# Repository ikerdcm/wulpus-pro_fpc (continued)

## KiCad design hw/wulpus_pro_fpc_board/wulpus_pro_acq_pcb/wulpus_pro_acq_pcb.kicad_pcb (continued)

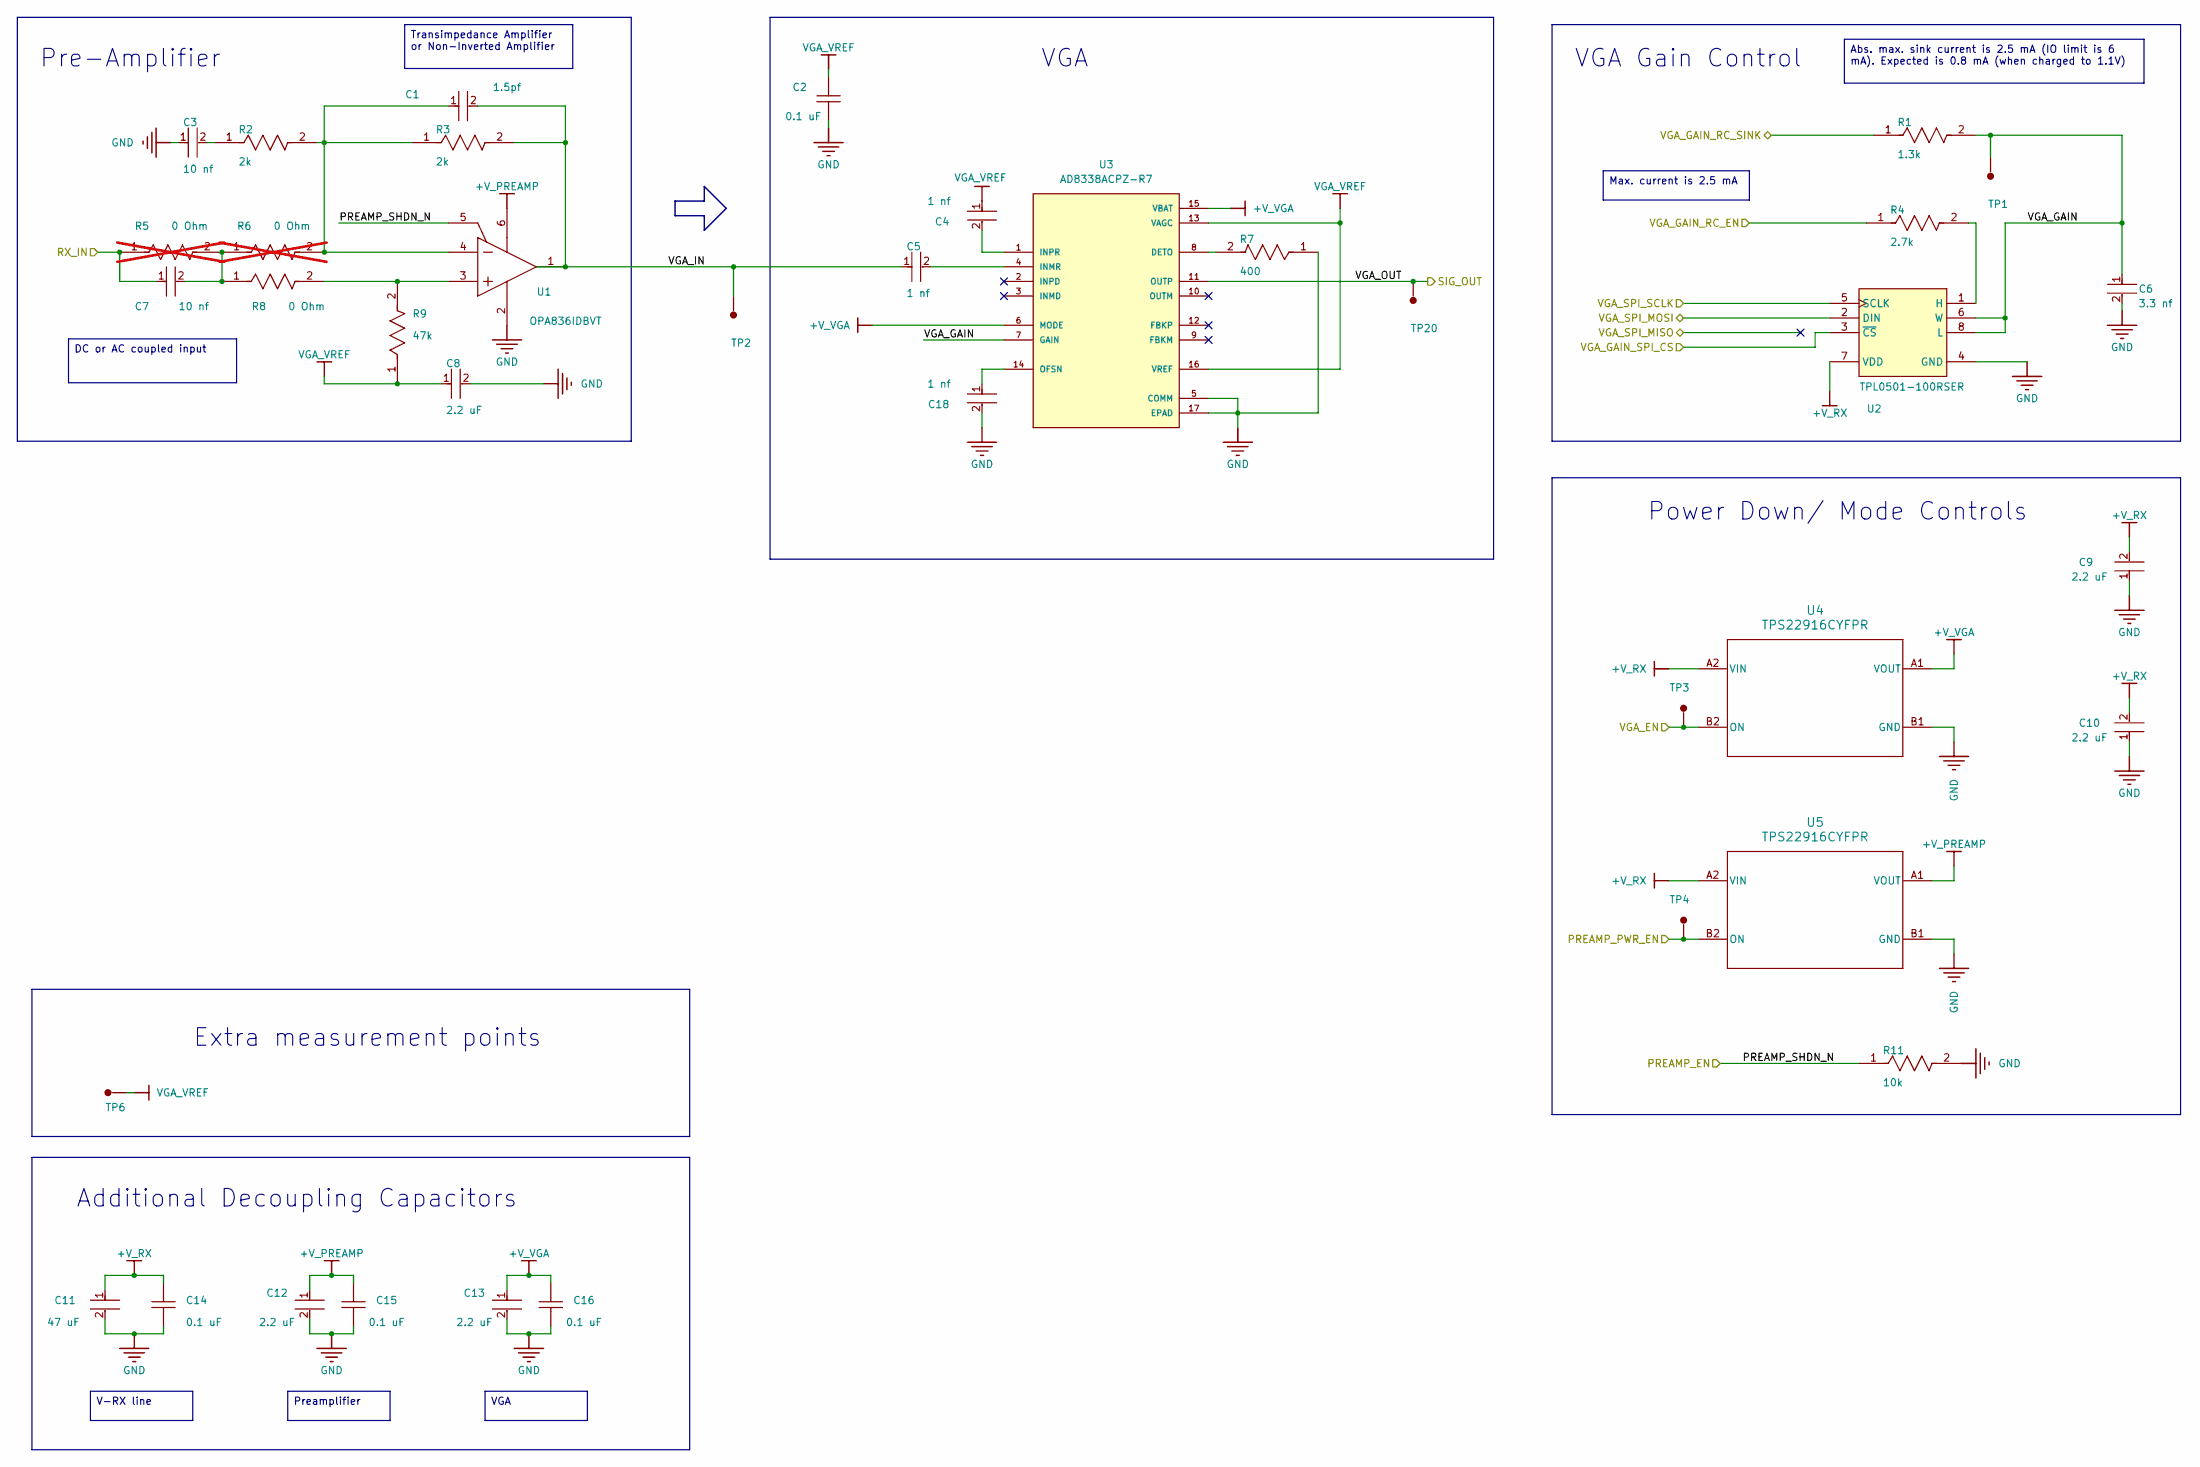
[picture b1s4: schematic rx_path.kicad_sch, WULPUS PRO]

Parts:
C1: 1.5pf; C_0402_1005Metric; VOLTAGE RATING 50V; VOLTAGE RATING (DC) 50V; PART NUMBER GJM1555C1H1R5BB01D
C2, C14, C15, C16: 0.1 uF; C_0402_1005Metric; PART NUMBER C0402C104K4RACTU
C3, C7: 10 nf; C_0402_1005Metric; VOLTAGE 10V; VOLTAGE RATING (DC) 10V; PART NUMBER GRM033R71A103KA01D
C4, C5, C18: 1 nf; C_0402_1005Metric; TOLERANCE 5%; VOLTAGE RATING 50V; PART NUMBER GRM1555C1H102JA01D
C6: 3.3 nf; C_0402_1005Metric; VOLTAGE RATING 50V; TOLERANCE 5%; PART NUMBER 04025C332JAT2A
C8, C9, C10, C12, C13: 2.2 uF; C_0402_1005Metric; VOLTAGE RATING 10V; VOLTAGE RATING (DC) 10V; PART NUMBER C1005X7S1A225K050BC
C11: 47 uF; C_0603_1608Metric; TOLERANCE 20%; VOLTAGE RATING (DC) 6.3V; PART NUMBER GRM188R60J476ME01D
R1: 1.3k; R_0402_1005Metric; TOLERANCE 5%; VOLTAGE RATING (DC) 50V; MPN CRCW04021K30JNED
R2, R3: 2k; R_0402_1005Metric; WORKING VOLTAGE 50V; POWER RATING 100mW; MPN ERJ-2RKF2001X
R4: 2.7k; R_0402_1005Metric; TOLERANCE 1%; MPN MCS04020C2701FE000
R5, R6: 0 Ohm; R_0402_1005Metric; TOLERANCE 5%; VOLTAGE RATING 50V; MPN CRCW04020000Z0ED; not fitted
R7: 400; R_0402_1005Metric; TOLERANCE 1%; VOLTAGE RATING 50V; MPN CRCW04021R00FKEDC
R8: 0 Ohm; R_0402_1005Metric; TOLERANCE 5%; VOLTAGE RATING 50V; MPN CRCW04020000Z0ED
R9: 47k; R_0402_1005Metric; POWER RATING 50mW; TOLERANCE 5%; MPN CRCW040247K0JNEE
R11: 10k; R_0402_1005Metric; VOLTAGE RATING 50V; POWER RATING 63mW; MPN CRCW040210K0JNED
TP1, TP2, TP3, TP4, TP6, TP20: TP-SM-C-100; TestPoint_Pad_D1.0mm
U1: OPA836IDBVT; SOT-23-6_Handsoldering; PARTNUMBER OPA836IDBVT
U2: TPL0501-100RSER; Texas_UQFN-8_1.5x1.5mm_P0.5mm; PARTNUMBER TPL0501-100RSER
U3: AD8338ACPZ-R7; QFN50P300X300X80-17N; PARTREV B; DigiKey_Part_Number 505-AD8338ACPZ-R7CT-ND
U4, U5: TPS22916CYFPR; YFP0004ABAB; MPN TPS22916CYFPR; LCSC C2680319

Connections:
+V_PREAMP: C12.1, C15.2, U1.6 (VS+), U5.A1 (VOUT)
+V_RX: C9.2, C10.2, C11.1, C14.2, U2.7 (VDD), U4.A2 (VIN), U5.A2 (VIN); also elsewhere on the board
+V_VGA: C13.1, C16.2, U3.6 (MODE), U3.15 (VBAT), U4.A1 (VOUT)
/U_hv_mux_tr_sw/HV_MUX_SPI_MISO: U2.2 (DIN); also elsewhere on the board
/U_hv_mux_tr_sw/HV_MUX_SPI_SCLK: U2.5 (SCLK); also elsewhere on the board
/U_hv_mux_tr_sw/RX_OUT: C7.1, R5.1; also elsewhere on the board
/U_msp430/PREAMP_PWR_EN: TP4.1 (1_1), U5.B2 (ON); also elsewhere on the board
/U_msp430/VGA_GAIN_RC_EN: R4.1; also elsewhere on the board
/U_msp430/VGA_GAIN_RC_SINK: R1.1; also elsewhere on the board
/U_msp430/VGA_GAIN_SPI_CS: U2.3 (~CS); also elsewhere on the board
/U_msp430/VGA_PWR_EN: TP3.1, U4.B2 (ON); also elsewhere on the board
/U_rx_path/PREAMP_SHDN_N: R11.1, U1.5 (~PD); also elsewhere on the board
/U_rx_path/VGA_GAIN: C6.1, R1.2, TP1.1, U2.6 (W), U2.8 (L), U3.7 (GAIN)
/U_rx_path/VGA_IN: C1.2, C5.1, R3.2, TP2.1 (1_1), U1.1 (VOUT)
/U_rx_path/VGA_OUT: TP20.1 (1_1), U3.11 (OUTP); also elsewhere on the board
GND: C2.1, C3.1, C6.2, C8.2, C9.1, C10.1, C11.2, C12.2, C13.2, C14.1, C15.1, C16.1, C18.2, R7.1, R11.2, U1.2 (VS-), U2.4 (GND), U3.5 (COMM), U3.17 (EPAD), U4.B1 (GND), U5.B1 (GND); also elsewhere on the board
unnamed: C3.2, R2.1
unnamed: C7.2, R5.2, R6.1, R8.1
unnamed: R8.2, R9.2, U1.3 (VIN+)
unnamed: C1.1, R2.2, R3.1, R6.2, U1.4 (VIN-)
unnamed: R4.2, U2.1 (H)
unnamed: R7.2, U3.8 (DETO)
unnamed: C5.2, U3.4 (INMR)
unnamed: C4.2, U3.1 (INPR)
unnamed: C18.1, U3.14 (OFSN)
VGA_VREF: C2.2, C4.1, C8.1, R9.1, TP6.1 (1_1), U3.13 (VAGC), U3.16 (VREF)

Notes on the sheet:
VGA Gain Control
Power Down/ Mode Controls
Additional Decoupling Capacitors
Pre-Amplifier
Extra measurement points
VGA
Max. current is 2.5 mA
V-RX line
Abs. max. sink current is 2.5 mA (IO limit is 6 mA). Expected is 0.8 mA (when charged to 1.1V)
DC or AC coupled input
Preamplifier
Transimpedance Amplifier or Non-Inverted Amplifier

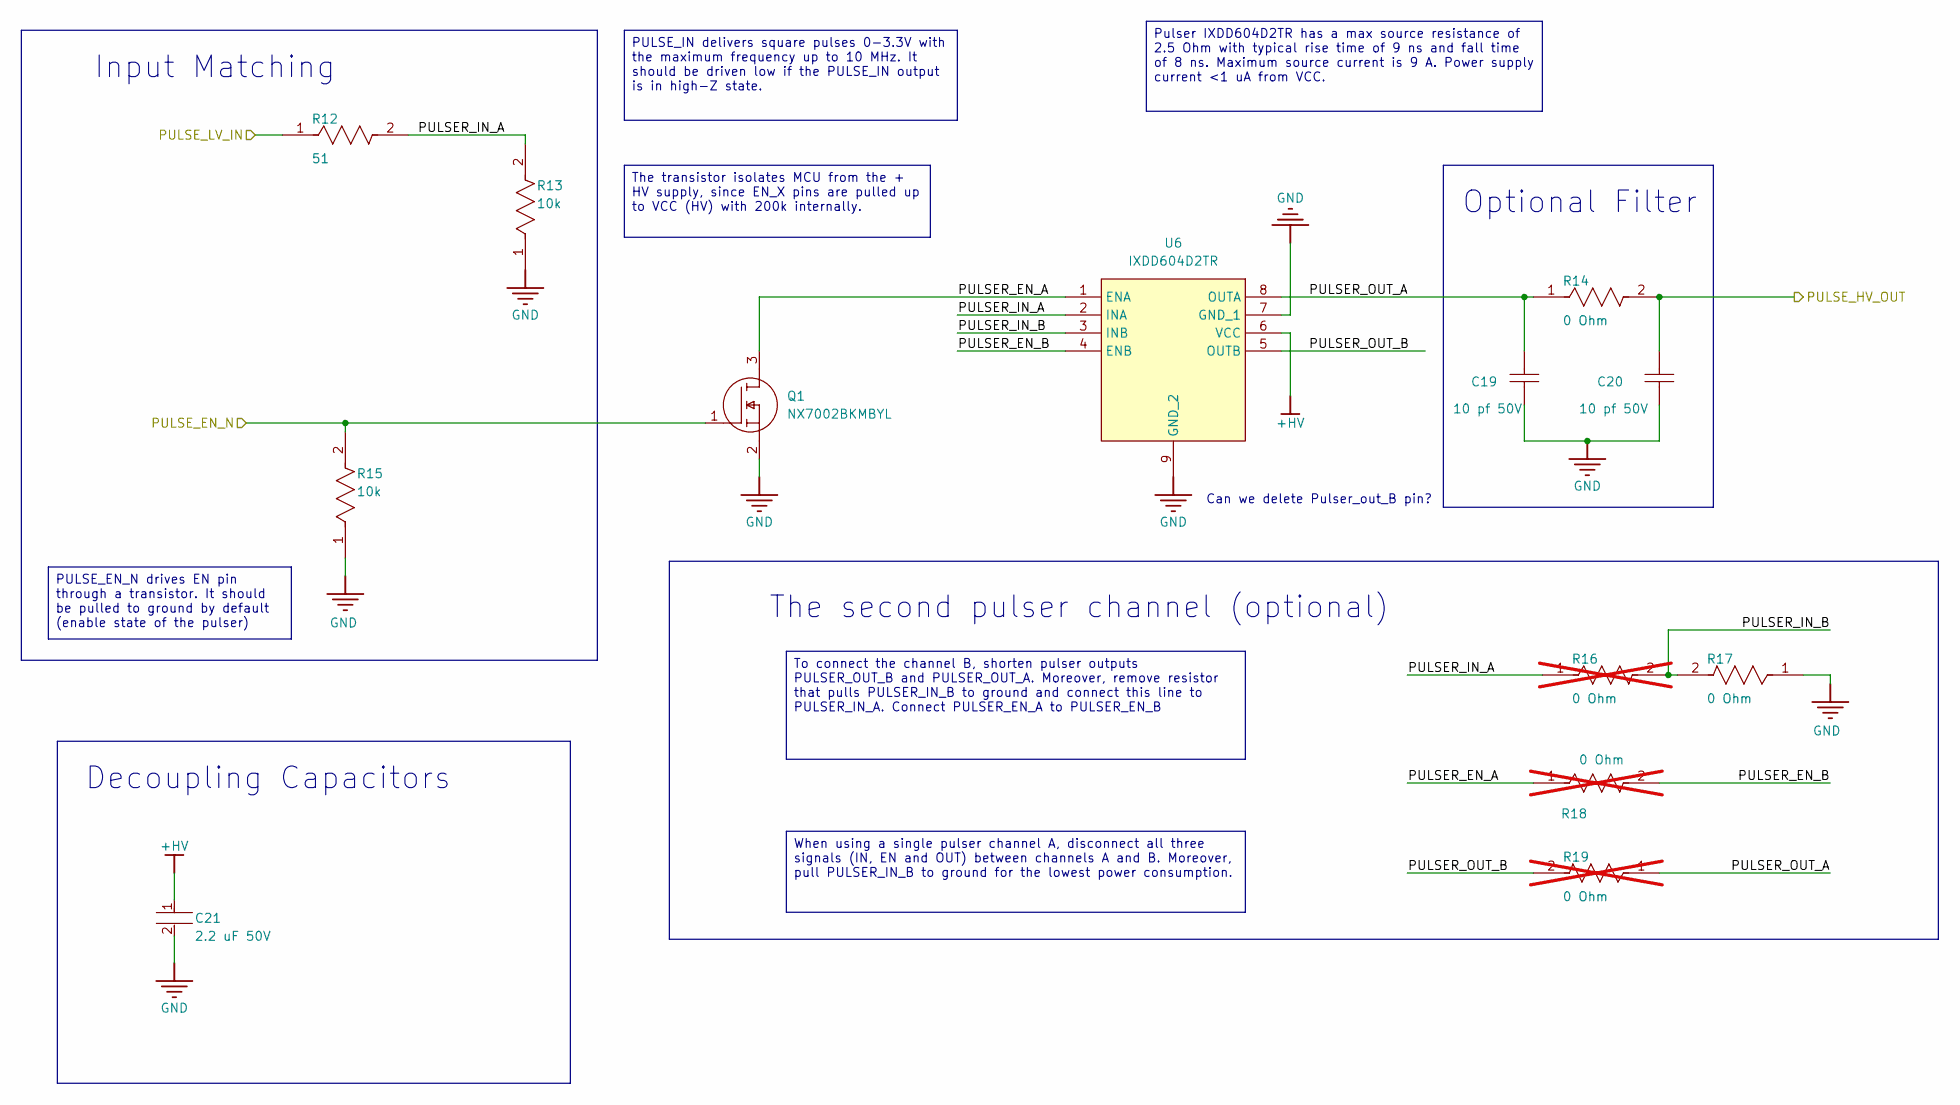
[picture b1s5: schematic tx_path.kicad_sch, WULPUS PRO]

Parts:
C19, C20: 10 pf 50V; C_0402_1005Metric; PART NUMBER GRM1555C1H100JA01D
C21: 2.2 uF 50V; C_0603_1608Metric; VOLTAGE RATING (DC) 50V; TOLERANCE 20%; PART NUMBER GRM188R61H225ME11D
Q1: NX7002BKMBYL; Diodes_DFN1006-3; MANUFACTURER_PART_NUMBER NX7002BKMBYL; MOUSER PART NUMBER 771-NX7002BKMBYL
R12: 51; R_0402_1005Metric; TOLERANCE 5%; POWER RATING 63mW; MPN CRCW040251R0JNED
R13, R15: 10k; R_0402_1005Metric; VOLTAGE RATING 50V; POWER RATING 63mW; MPN CRCW040210K0JNED
R14: 0 Ohm; R_0603_1608Metric; TOLERANCE 5%; VOLTAGE RATING 75V; MANUFACTURER PART NUMBER ERJ-3GEY0R00V; MOUSER DESCRIPTION Resistor, Chip Thick Film, 0 Ohm, 0.1w,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
R16, R18, R19: 0 Ohm; R_0402_1005Metric; TOLERANCE 5%; VOLTAGE RATING 50V; MPN CRCW04020000Z0ED; not fitted
R17: 0 Ohm; R_0402_1005Metric; TOLERANCE 5%; VOLTAGE RATING 50V; MPN CRCW04020000Z0ED
U6: IXDD604D2TR; IXYS_DFN-8_IXY; MANUFACTURER_PART_NUMBER IXDD604D2TR; MOUSER PART NUMBER 849-IXDD604D2TR

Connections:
+HV: C21.1, U6.6 (VCC); also elsewhere on the board
/U_hv_mux_tr_sw/TX_HV_PULSE_IN: C20.2, R14.2; also elsewhere on the board
/U_msp430/PULSER_HIZ_EN: Q1.1 (G), R15.2; also elsewhere on the board
/U_msp430/PULSER_OUT: R12.1; also elsewhere on the board
/U_tx_path/PULSER_EN_A: Q1.3 (D), R18.1, U6.1 (ENA)
/U_tx_path/PULSER_EN_B: R18.2, U6.4 (ENB)
/U_tx_path/PULSER_IN_A: R12.2, R13.2, R16.1, U6.2 (INA)
/U_tx_path/PULSER_IN_B: R16.2, R17.2, U6.3 (INB)
/U_tx_path/PULSER_OUT_A: C19.2, R14.1, R19.1, U6.8 (OUTA)
/U_tx_path/PULSER_OUT_B: R19.2, U6.5 (OUTB)
GND: C19.1, C20.1, C21.2, Q1.2 (S), R13.1, R15.1, R17.1, U6.7 (GND_1), U6.9 (GND_2); also elsewhere on the board

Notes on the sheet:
Can we delete Pulser_out_B pin?
The second pulser channel (optional)
Decoupling Capacitors
Input Matching
Optional Filter
PULSE_EN_N drives EN pin through a transistor. It should be pulled to ground by default (enable state of the pulser)
To connect the channel B, shorten pulser outputs PULSER_OUT_B and PULSER_OUT_A. Moreover, remove resistor that pulls PULSER_IN_B to ground and connect this line to PULSER_IN_A. Connect PULSER_EN_A to PULSER_EN_B
The transistor isolates MCU from the + HV supply, since EN_X pins are pulled up to VCC (HV) with 200k internally.
PULSE_IN delivers square pulses 0-3.3V with the maximum frequency up to 10 MHz. It should be driven low if the PULSE_IN output is in high-Z state.
Pulser IXDD604D2TR has a max source resistance of 2.5 Ohm with typical rise time of 9 ns and fall time of 8 ns. Maximum source current is 9 A. Power supply current <1 uA from VCC.
When using a single pulser channel A, disconnect all three signals (IN, EN and OUT) between channels A and B. Moreover, pull PULSER_IN_B to ground for the lowest power consumption.

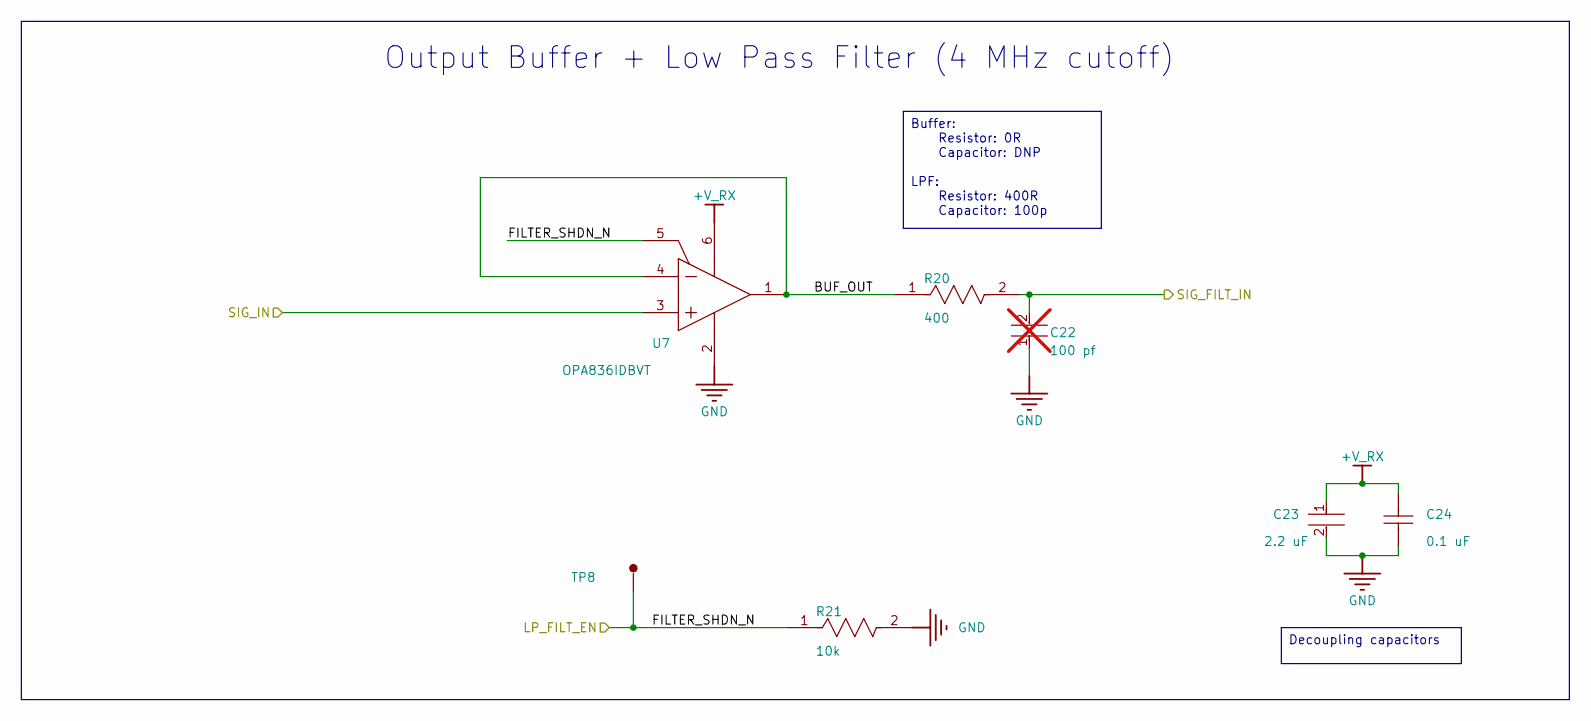
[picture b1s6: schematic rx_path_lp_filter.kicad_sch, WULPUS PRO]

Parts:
C22: 100 pf; C_0402_1005Metric; VOLTAGE 50V; TOLERANCE 1%; PART NUMBER 04025A101FAT2A; not fitted
C23: 2.2 uF; C_0402_1005Metric; VOLTAGE RATING 10V; VOLTAGE RATING (DC) 10V; PART NUMBER C1005X7S1A225K050BC
C24: 0.1 uF; C_0402_1005Metric; PART NUMBER C0402C104K4RACTU
R20: 400; R_0402_1005Metric; TOLERANCE 1%; VOLTAGE RATING 50V; MPN CRCW04021R00FKEDC
R21: 10k; R_0402_1005Metric; VOLTAGE RATING 50V; POWER RATING 63mW; MPN CRCW040210K0JNED
TP8: TP-SM-C-100; TestPoint_Pad_D1.0mm
U7: OPA836IDBVT; SOT-23-6_Handsoldering; PARTNUMBER OPA836IDBVT

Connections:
+V_RX: C23.1, C24.2, U7.6 (VS+); also elsewhere on the board
/U_msp430/ADC_IN: C22.2, R20.2; also elsewhere on the board
/U_rx_path/VGA_OUT: U7.3 (VIN+); also elsewhere on the board
/U_rx_path_lp_filter/BUF_OUT: R20.1, U7.1 (VOUT), U7.4 (VIN-)
/U_rx_path_lp_filter/FILTER_SHDN_N: R21.1, TP8.1, U7.5 (~PD); also elsewhere on the board
GND: C22.1, C23.2, C24.1, R21.2, U7.2 (VS-); also elsewhere on the board

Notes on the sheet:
Output Buffer + Low Pass Filter (4 MHz cutoff)
Decoupling capacitors
Buffer: Resistor: 0R Capacitor: DNP LPF: Resistor: 400R Capacitor: 100p

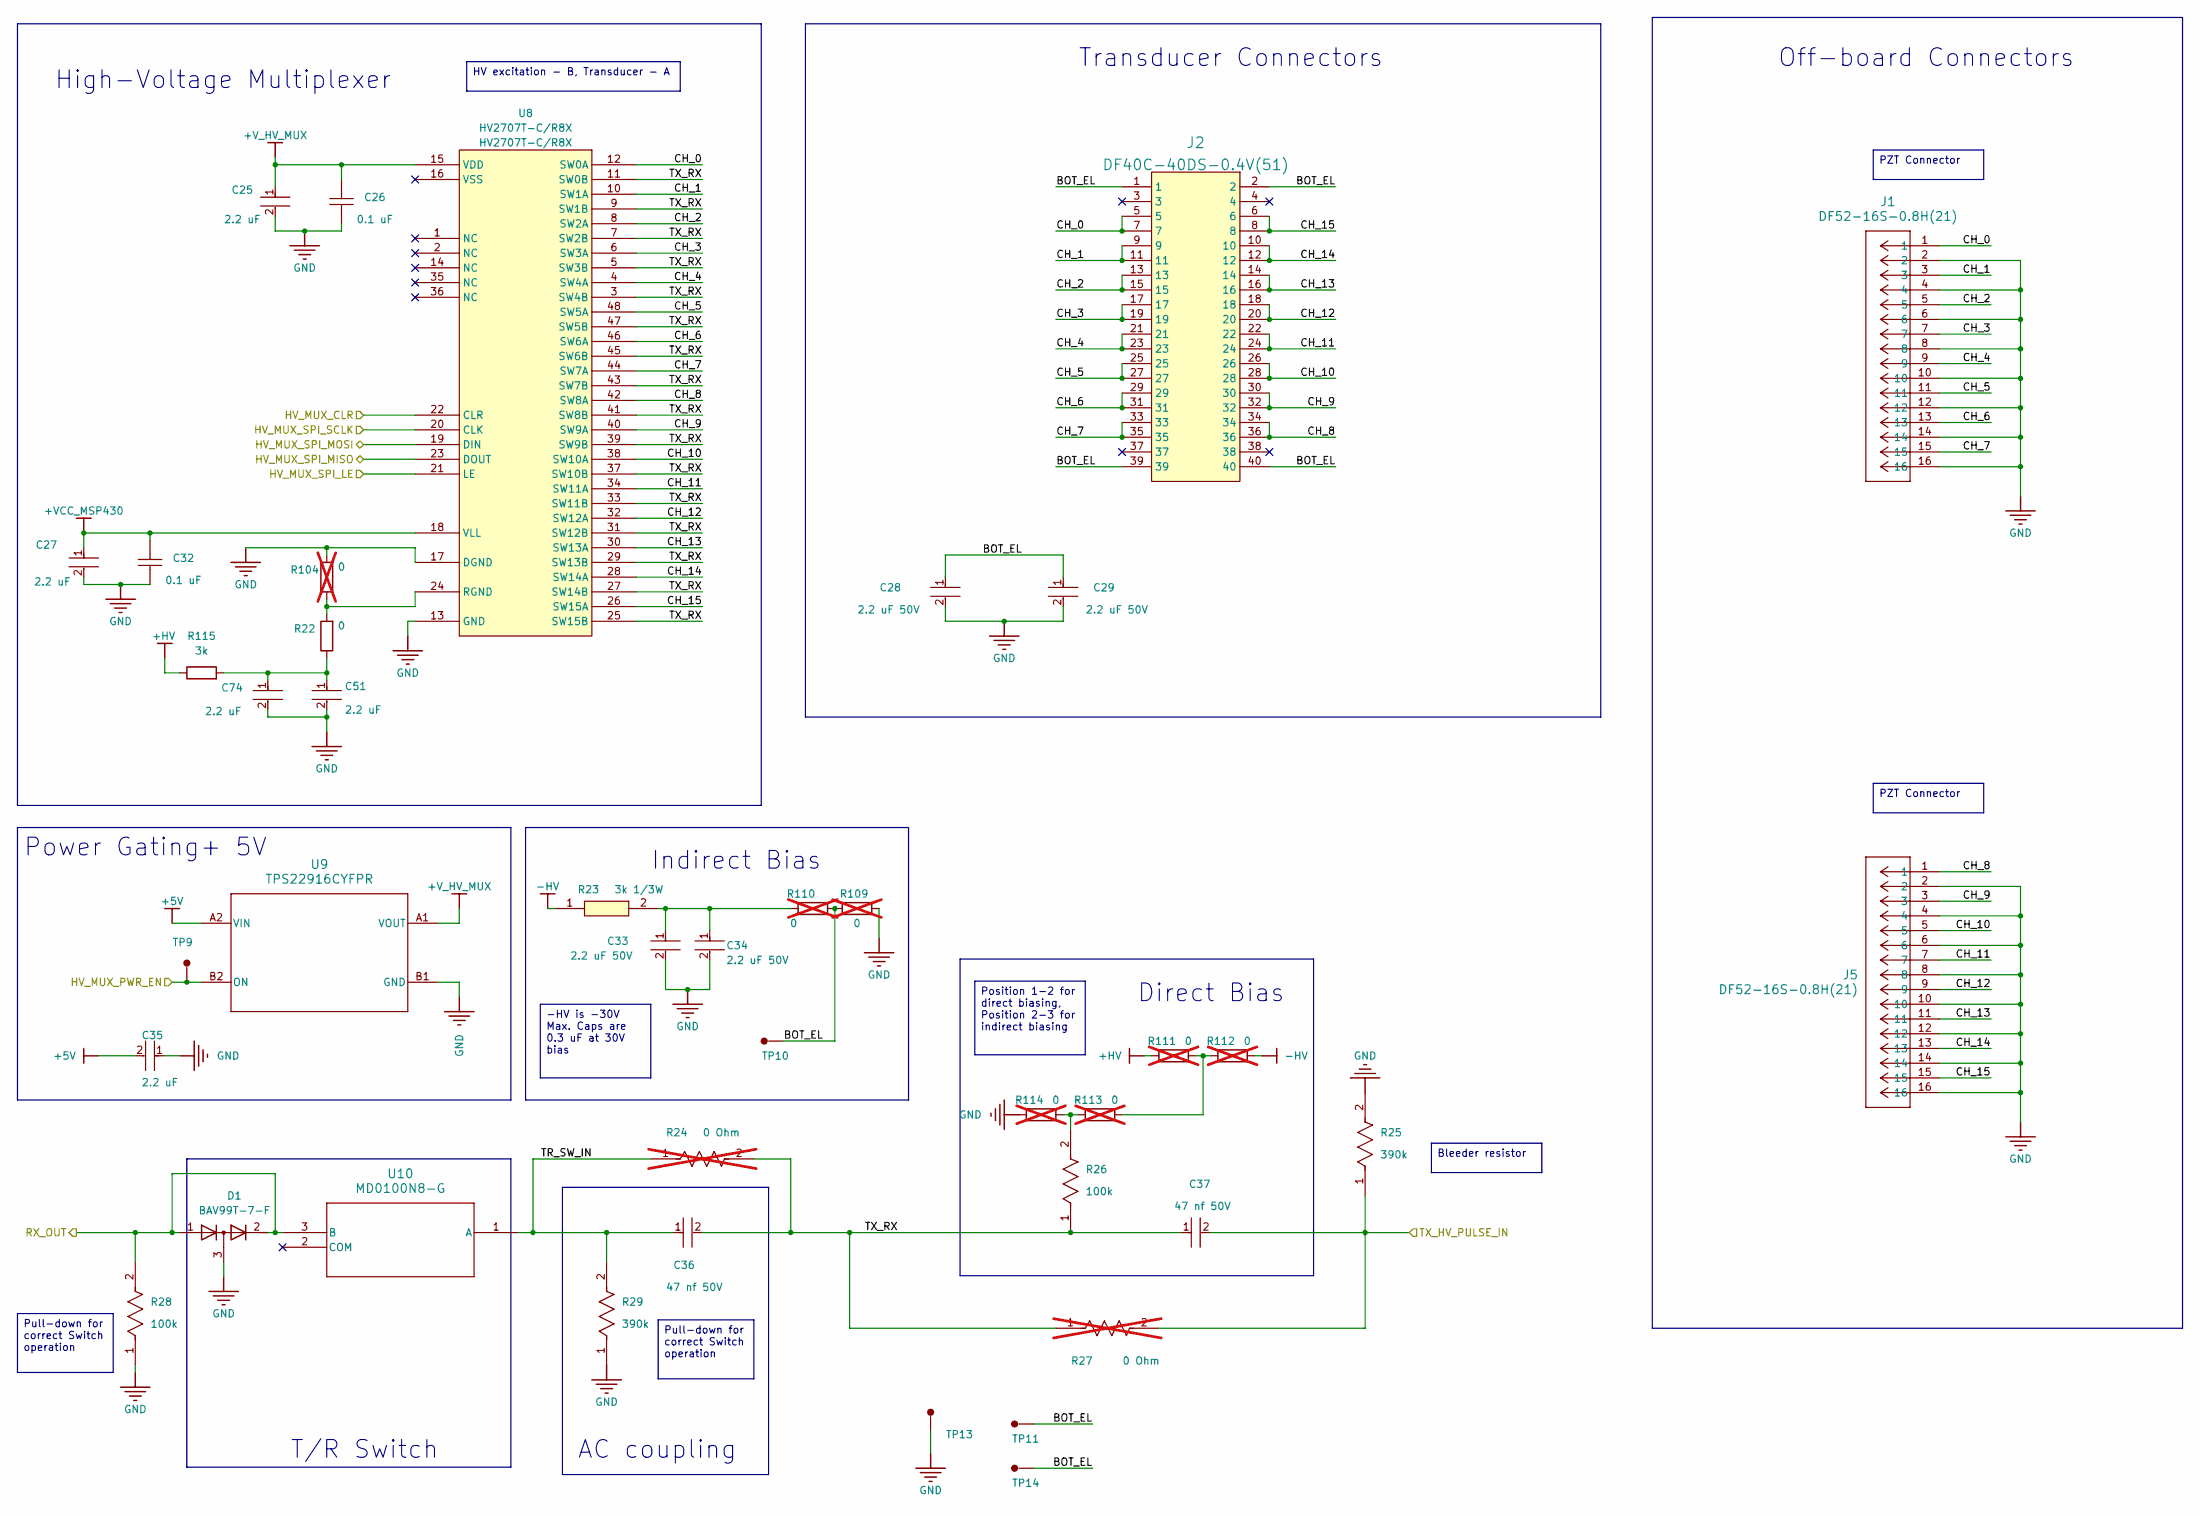
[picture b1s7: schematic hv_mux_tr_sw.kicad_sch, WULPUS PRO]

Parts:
C25, C27, C35, C51, C74: 2.2 uF; C_0402_1005Metric; VOLTAGE RATING 10V; VOLTAGE RATING (DC) 10V; PART NUMBER C1005X7S1A225K050BC
C26, C32: 0.1 uF; C_0402_1005Metric; PART NUMBER C0402C104K4RACTU
C28, C29, C33, C34: 2.2 uF 50V; C_0603_1608Metric; VOLTAGE RATING (DC) 50V; TOLERANCE 20%; PART NUMBER GRM188R61H225ME11
C36, C37: 47 nf 50V; C_0402_1005Metric; TOLERANCE 20%; VOLTAGE RATING (DC) 50V; PART NUMBER GRM155R71H473ME14D
D1: BAV99T-7-F; SOT-523; MPN BAV99T-7-F
J1, J5: DF52-16S-0.8H(21); CONN_DF52-16S-0.8H21_HIR; MPN DF52-16S-0.8H(21); LCSC C22281399
J2: DF40C-40DS-0.4V(51); Hirose_DF40C-40DS-0.4V_2x20_P0.4mm; MPN DF40C-40DS-0.4V(51)
R22: 0; R_0402_1005Metric; Tolerance 5%; MPN ERJ-2GE0R00X; LCSC C17168
R23: 3k 1/3W; R_0603_1608Metric; MANUFACTURER_PART_NUMBER ERJ-PA3J302V; MOUSER PART NUMBER 667-ERJ-PA3J302V
R24, R27: 0 Ohm; R_0402_1005Metric; TOLERANCE 5%; VOLTAGE RATING 50V; MPN CRCW04020000Z0ED; not fitted
R25, R29: 390k; R_0402_1005Metric; VOLTAGE RATING (DC) 50V; TOLERANCE 1%; MPN RC1005F394CS
R26, R28: 100k; R_0402_1005Metric; VOLTAGE RATING (DC) 50V; TOLERANCE 1%; MPN ERJ-2RKF1003X
R104, R109, R110, R111, R112, R113, R114: 0; R_0402_1005Metric; Tolerance 5%; MPN ERJ-2GE0R00X; LCSC C17168; not fitted
R115: 3k; R_0402_1005Metric; MPN CRCW06033K00FKEAHP
TP9, TP10, TP11, TP13, TP14: TP-SM-C-100; TestPoint_Pad_D1.0mm
U8: HV2707T-C/R8X; LQFP-48_7x7mm_P0.5mm; MANUFACTURER PART NUMBER HV2707T-C/R8X; LCSC C3656525
U9: TPS22916CYFPR; YFP0004ABAB; MPN TPS22916CYFPR; LCSC C2680319
U10: MD0100N8-G; TO-243AA_MCH; MPN MD0100N8-G; LCSC C629131

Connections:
+5V: C35.2, U9.A2 (VIN); also elsewhere on the board
+HV: R111.1, R115.1; also elsewhere on the board
+VBAT_STM: C27.1, C32.2, U8.18 (VLL); also elsewhere on the board
+V_HV_MUX: C25.1, C26.2, U8.15 (VDD), U9.A1 (VOUT)
-HV: R23.1, R112.2; also elsewhere on the board
/U_hv_mux_tr_sw/BOT_EL: C28.1, C29.1, J2.1, J2.2, J2.39, J2.40, R109.1, R110.2, TP10.1 (1_1), TP11.1 (1_1), TP14.1 (1_1)
/U_hv_mux_tr_sw/CH_0: J1.1, J2.5, J2.7, U8.12 (SW0A)
/U_hv_mux_tr_sw/CH_1: J1.3, J2.9, J2.11, U8.10 (SW1A)
/U_hv_mux_tr_sw/CH_2: J1.5, J2.13, J2.15, U8.8 (SW2A)
/U_hv_mux_tr_sw/CH_3: J1.7, J2.17, J2.19, U8.6 (SW3A)
/U_hv_mux_tr_sw/CH_4: J1.9, J2.21, J2.23, U8.4 (SW4A)
/U_hv_mux_tr_sw/CH_5: J1.11, J2.25, J2.27, U8.48 (SW5A)
/U_hv_mux_tr_sw/CH_6: J1.13, J2.29, J2.31, U8.46 (SW6A)
/U_hv_mux_tr_sw/CH_7: J1.15, J2.33, J2.35, U8.44 (SW7A)
/U_hv_mux_tr_sw/CH_8: J2.34, J2.36, J5.1, U8.42 (SW8A)
/U_hv_mux_tr_sw/CH_9: J2.30, J2.32, J5.3, U8.40 (SW9A)
/U_hv_mux_tr_sw/CH_10: J2.26, J2.28, J5.5, U8.38 (SW10A)
/U_hv_mux_tr_sw/CH_11: J2.22, J2.24, J5.7, U8.34 (SW11A)
/U_hv_mux_tr_sw/CH_12: J2.18, J2.20, J5.9, U8.32 (SW12A)
/U_hv_mux_tr_sw/CH_13: J2.14, J2.16, J5.11, U8.30 (SW13A)
/U_hv_mux_tr_sw/CH_14: J2.10, J2.12, J5.13, U8.28 (SW14A)
/U_hv_mux_tr_sw/CH_15: J2.6, J2.8, J5.15, U8.26 (SW15A)
/U_hv_mux_tr_sw/HV_MUX_CLR: U8.22 (CLR); also elsewhere on the board
/U_hv_mux_tr_sw/HV_MUX_PWR_EN: TP9.1 (1_1), U9.B2 (ON); also elsewhere on the board
/U_hv_mux_tr_sw/HV_MUX_SPI_LE: U8.21 (LE); also elsewhere on the board
/U_hv_mux_tr_sw/HV_MUX_SPI_MISO: U8.23 (DOUT); also elsewhere on the board
/U_hv_mux_tr_sw/HV_MUX_SPI_MOSI: U8.19 (DIN); also elsewhere on the board
/U_hv_mux_tr_sw/HV_MUX_SPI_SCLK: U8.20 (CLK); also elsewhere on the board
/U_hv_mux_tr_sw/RX_OUT: D1.1 (A), D1.2 (K), R28.2, U10.3 (B); also elsewhere on the board
/U_hv_mux_tr_sw/TR_SW_IN: C36.1, R24.1, R29.2, U10.1 (A)
/U_hv_mux_tr_sw/TX_HV_PULSE_IN: C37.2, R25.1, R27.2; also elsewhere on the board
/U_hv_mux_tr_sw/TX_RX: C36.2, C37.1, R24.2, R26.1, R27.1, U8.3 (SW4B), U8.5 (SW3B), U8.7 (SW2B), U8.9 (SW1B), U8.11 (SW0B), U8.25 (SW15B), U8.27 (SW14B), U8.29 (SW13B), U8.31 (SW12B), U8.33 (SW11B), U8.37 (SW10B), U8.39 (SW9B), U8.41 (SW8B), U8.43 (SW7B), U8.45 (SW6B), U8.47 (SW5B)
GND: C25.2, C26.1, C27.2, C28.2, C29.2, C32.1, C33.2, C34.2, C35.1, C51.2, C74.2, D1.3 (common), J1.2, J1.4, J1.6, J1.8, J1.10, J1.12, J1.14, J1.16, J5.2, J5.4, J5.6, J5.8, J5.10, J5.12, J5.14, J5.16, R25.2, R28.1, R29.1, R104.2, R109.2, R114.1, TP13.1 (1_1), U8.13 (GND), U8.17 (DGND), U9.B1 (GND); also elsewhere on the board
unnamed: C33.1, C34.1, R23.2, R110.1
unnamed: C51.1, C74.1, R22.1, R115.2
unnamed: R111.2, R112.1, R113.2
unnamed: R26.2, R113.1, R114.2
unnamed: R22.2, R104.1, U8.24 (RGND)

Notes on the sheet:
Direct Bias
High-Voltage Multiplexer
Power Gating+ 5V
AC coupling
Transducer Connectors
T/R Switch
Off-board Connectors
Indirect Bias
Bleeder resistor
-HV is -30V Max. Caps are 0.3 uF at 30V bias
Position 1-2 for direct biasing, Position 2-3 for indirect biasing
HV excitation - B, Transducer - A
PZT Connector
Pull-down for correct Switch operation

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
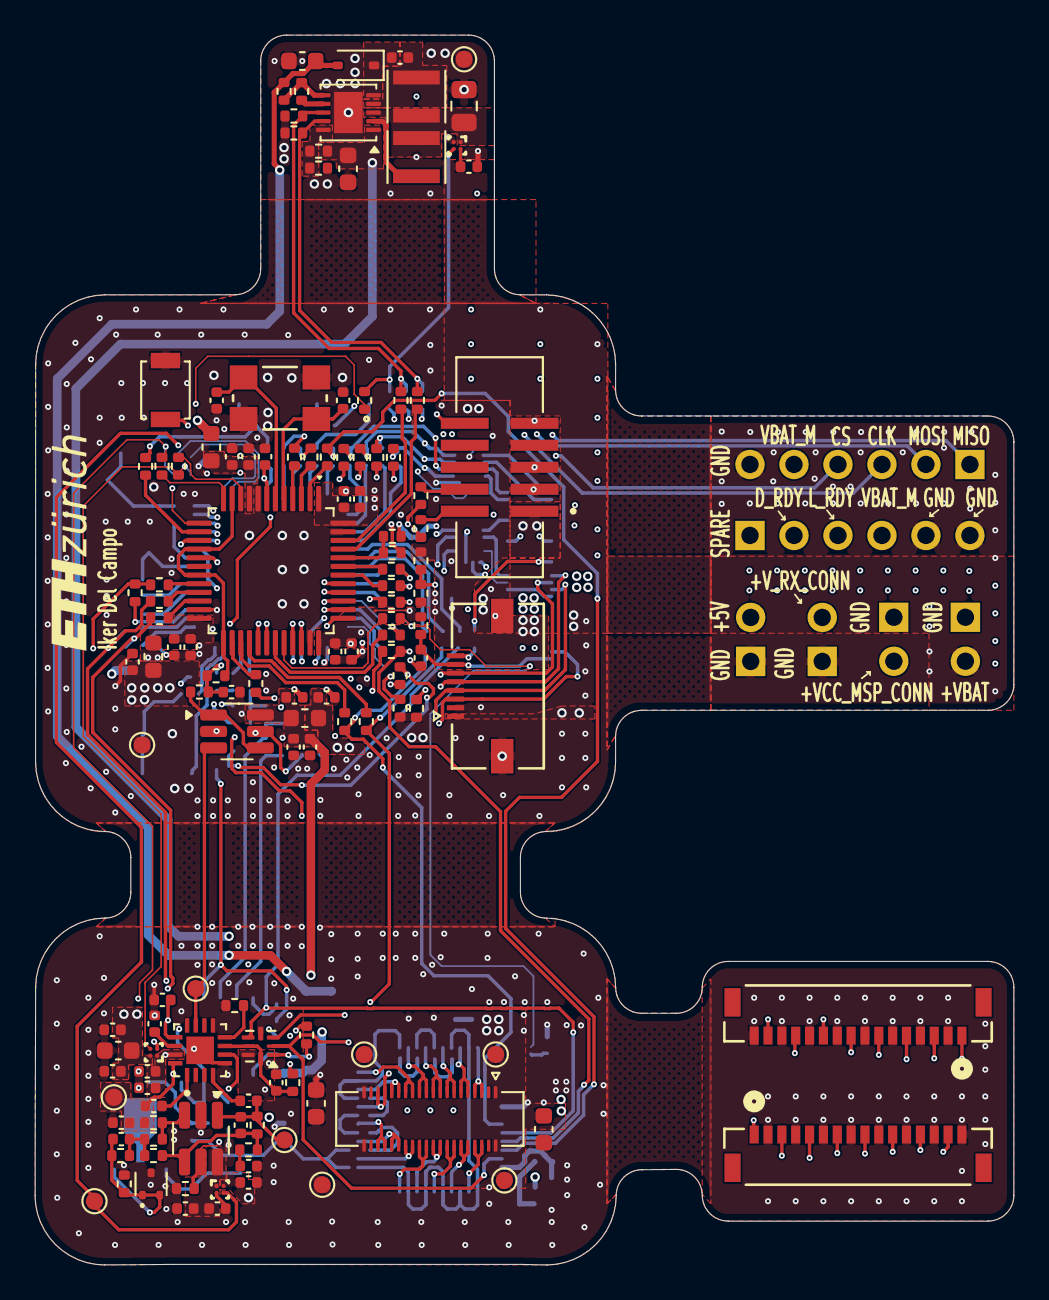
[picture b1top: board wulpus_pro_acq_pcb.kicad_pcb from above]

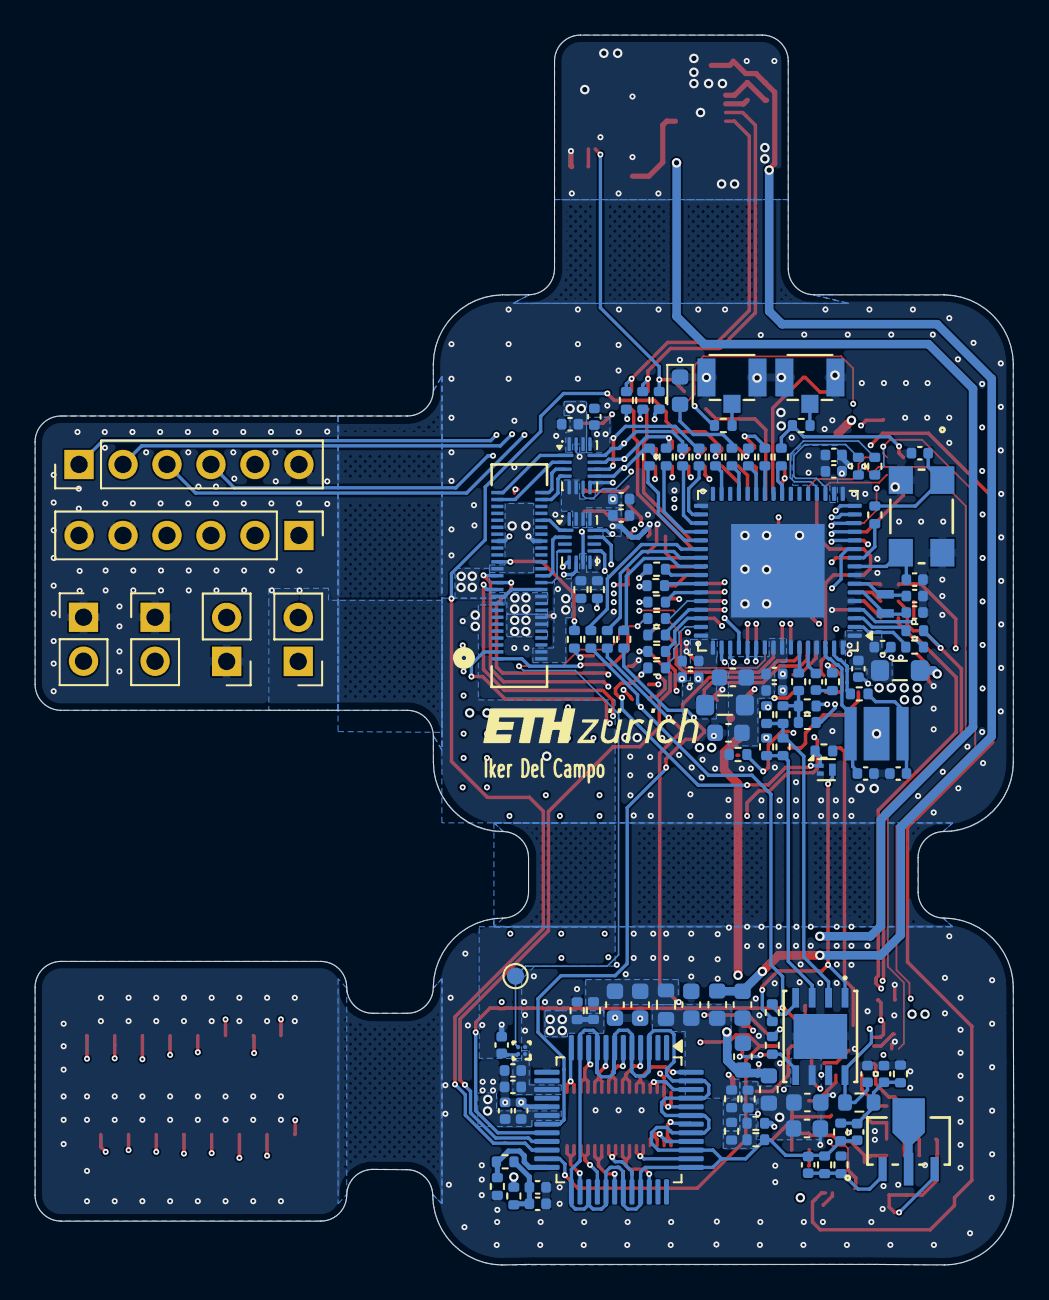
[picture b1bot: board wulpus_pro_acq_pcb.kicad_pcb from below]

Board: 4 copper layers, 56.5 x 71.0 mm, 258 parts (127 on the bottom side), 195 nets.

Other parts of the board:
ART1#2: ETH Zurich Logo silkscreen; ETH_zurich_2mm
C17: 2.2uF; C_0402_1005Metric
C56, C57, C58, C60, C61, C62: 2.2 uF 50V; C_0603_1608Metric
C59: 1 uF 50V; C_0805_2012Metric
C63: 0.1 uF 50V; C_0402_1005Metric
C64, C65, C66, C67: 1 uF 10V; C_0402_1005Metric
D3: ZHCS400QTA; D_SOD-323
FB1, FB2, FB3, FB4: 100Ω@100MHz; L_0603_1608Metric
L3, L4: 10uH; IND_LQH3NPZ100MMEL
R38, R43: 1MΩ; R_0402_1005Metric
R39: 43.2 kΩ; R_0402_1005Metric
R40: 41.2 kΩ; R_0402_1005Metric
R41, R42: 10k; R_0402_1005Metric
U12: LT3463EDD#PBF; DFN-10-1EP_3x3mm_P0.5mm_EP1.65x2.38mm
U13: TPS22916CYFPR; YFP0004ABAB

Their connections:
+HV: C61.1, FB2.2; also elsewhere on the board
+VBAT: C17.2, U13.A2 (VIN); also elsewhere on the board
+VBAT_STM: C65.1, FB3.2; also elsewhere on the board
+VCC_MSP430_CONN: C64.1, FB3.1; also elsewhere on the board
+V_IN_HV: C59.1, L3.1, L4.1, U12.3 (VIN), U13.A1 (VOUT)
+V_RX: C67.1, FB4.2; also elsewhere on the board
+V_RX_CONN: C66.1, FB4.1; also elsewhere on the board
-HV: C57.1, FB1.2; also elsewhere on the board
/U_msp430/HV_PWR_EN: U13.B2 (ON); also elsewhere on the board
/U_power/HV_EN1: R41.1, U12.9 (~SHDN1); also elsewhere on the board
/U_power/HV_EN2: R42.1, U12.8 (~SHDN2); also elsewhere on the board
GND: C17.1, C56.2, C57.2, C58.2, C59.2, C60.2, C61.2, C62.2, C64.2, C65.2, C66.2, C67.2, R39.2, R41.2, R42.2, U12.11 (EP), U13.B1 (GND); also elsewhere on the board
unnamed: C63.1, D3.1 (K), U12.5 (D2)
unnamed: R38.1, R39.1, U12.10 (FB1)
unnamed: R40.2, R43.2, U12.6 (FB2)
unnamed: L3.2, U12.2 (SW1)
unnamed: C63.2, L4.2, U12.4 (SW2)
unnamed: R40.1, U12.7 (VREF)
VOUT_NEG: C56.1, C62.1, D3.2 (A), FB1.1, R43.1
VOUT_POS: C58.1, C60.1, FB2.1, R38.2, U12.1 (VOUT1)

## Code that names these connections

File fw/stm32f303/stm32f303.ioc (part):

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Mcu.Name=STM32F303C(B-C)Tx
Mcu.Package=LQFP48
Mcu.UserName=STM32F303CCTx
PA0.GPIOParameters=GPIO_Label
PA0.GPIO_Label=VGA_PWR_EN
PA0.Signal=GPIO_Output
PA1.Mode=IN2-Single-Ended
PA1.Signal=ADC1_IN2
PA10.GPIOParameters=GPIO_Label
PA10.GPIO_Label=TRIG_OUT
PA10.Signal=GPIO_Output
PA11.GPIOParameters=GPIO_Label
PA11.GPIO_Label=HV_MUX_PWR_EN
PA11.Signal=GPIO_Output
PA12.GPIOParameters=GPIO_Label
PA12.GPIO_Label=HOST_SPARE_PIN
PA12.Signal=GPIO_Output
PA13.Mode=Serial_Wire
PA13.Signal=SYS_JTMS-SWDIO
PA14.Mode=Serial_Wire
PA14.Signal=SYS_JTCK-SWCLK
PA15.GPIOParameters=GPIO_Label
PA15.GPIO_Label=HOST_SPI_CS
PA15.Signal=GPIO_Input
PA2.GPIOParameters=GPIO_Label
PA2.GPIO_Label=PREAMP_EN
PA2.Signal=GPIO_Output
PA3.GPIOParameters=GPIO_Label
PA3.GPIO_Label=HV_PWR_EN
PA3.Signal=GPIO_Output
PA4.GPIOParameters=GPIO_Label
PA4.GPIO_Label=UUPS_TRIG_IN
PA4.Signal=GPIO_Input
PA5.GPIOParameters=GPIO_Label
PA5.GPIO_Label=PULS_SPI_SCK
PA5.Mode=TX_Only_Simplex_Unidirect_Master
PA5.Signal=SPI1_SCK
PA6.Mode=IN3-Single-Ended
PA6.Signal=ADC2_IN3
PA7.GPIOParameters=GPIO_Label
PA7.GPIO_Label=PULS_SPI_MOSI
PA7.Mode=TX_Only_Simplex_Unidirect_Master
PA7.Signal=SPI1_MOSI
PA8.GPIOParameters=GPIO_Label
PA8.GPIO_Label=PULS_HIZ_EN
PA8.Signal=GPIO_Output
PA9.GPIOParameters=GPIO_Label
PA9.GPIO_Label=HV_MUX_SPI_CS
PA9.Signal=GPIO_Output
PB1.Mode=IN1-Single-Ended
PB1.Signal=ADC3_IN1
PB10.GPIOParameters=GPIO_Label
PB10.GPIO_Label=VGA_GAIN_RC_EN
PB10.Signal=GPIO_Output
PB11.GPIOParameters=GPIO_Label
PB11.GPIO_Label=VGA_GAIN_RC_SINK
PB11.Signal=GPIO_Input
PB12.Mode=IN3-Single-Ended
PB12.Signal=ADC4_IN3
PB13.GPIOParameters=GPIO_Label
PB13.GPIO_Label=CTRL_SPI_SCK
PB13.Mode=Full_Duplex_Master
PB13.Signal=SPI2_SCK
PB14.GPIOParameters=GPIO_Label
PB14.GPIO_Label=CTRL_SPI_MISO
PB14.Mode=Full_Duplex_Master
PB14.Signal=SPI2_MISO
PB15.GPIOParameters=GPIO_Label
PB15.GPIO_Label=CTRL_SPI_MOSI
PB15.Mode=Full_Duplex_Master
PB15.Signal=SPI2_MOSI
PB2.GPIOParameters=GPIO_Label
PB2.GPIO_Label=VGA_GAIN_SPI_CS
PB2.Signal=GPIO_Output
PB3.GPIOParameters=GPIO_Label
PB3.GPIO_Label=HOST_SPI_SCK
PB3.Mode=Full_Duplex_Slave
PB3.Signal=SPI3_SCK
PB4.GPIOParameters=GPIO_Label
PB4.GPIO_Label=HOST_SPI_MISO
PB4.Mode=Full_Duplex_Slave
PB4.Signal=SPI3_MISO
PB5.GPIOParameters=GPIO_Label
PB5.GPIO_Label=HOST_SPI_MOSI
PB5.Mode=Full_Duplex_Slave
PB5.Signal=SPI3_MOSI
PB6.GPIOParameters=GPIO_Label
PB6.GPIO_Label=HOST_DATA_READY
PB6.Signal=GPIO_Output
PB7.GPIOParameters=GPIO_Label
PB7.GPIO_Label=HOST_LINK_READY
PB7.Signal=GPIO_Input
PB8.GPIOParameters=GPIO_Label
PB8.GPIO_Label=HV_POS_EN
PB8.Signal=GPIO_Output
PB9.GPIOParameters=GPIO_Label
PB9.GPIO_Label=HV_NEG_EN
PB9.Signal=GPIO_Output
PC13.GPIOParameters=GPIO_Label
PC13.GPIO_Label=HV_MUX_CLR
PC13.Signal=GPIO_Output
PC14-OSC32_IN.GPIOParameters=GPIO_Label
PC14-OSC32_IN.GPIO_Label=LP_FILT_EN
PC14-OSC32_IN.Signal=GPIO_Output
PC15-OSC32_OUT.GPIOParameters=GPIO_Label
PC15-OSC32_OUT.GPIO_Label=PREAMP_PWR_EN
PC15-OSC32_OUT.Signal=GPIO_Output
PF0-OSC_IN.Mode=HSE-External-Oscillator
PF0-OSC_IN.Signal=RCC_OSC_IN
PF1-OSC_OUT.Mode=HSE-External-Oscillator
PF1-OSC_OUT.Signal=RCC_OSC_OUT
RCC.HSEPLLFreq_Value=8000000
RCC.HSE_VALUE=8000000
RCC.SYSCLKFreq_VALUE=72000000
RCC.SYSCLKSourceVirtual=RCC_SYSCLKSOURCE_PLLCLK
board=custom

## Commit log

2026-03-08 Migration to KiCad initiated
2026-03-12 Migration of WULPUS Pro completed
2026-03-19 Schematics finished, waiting for approval. PCB Placement started
2026-03-23 Placement of all modules except PWR and PWR MUX completed
2026-03-25 One transducer connector removed (only one remains); SWD connector for STM changed; Advances in the placement
2026-03-28 KiCad 10 migration; Board outline difined; Routing continued
2026-04-01 Routing of all PCB except VBAT completed; DRC yet to pass
2026-04-06 Routing finished, Via stitching done; DRC passed except solder mask issues; Teardrops not added because pourings don't recognise them
2026-04-08 Silkscreen added; Via corrections; BOM corrections; Fabrication files generated
2026-04-08 Stainless Steel Stiffener version added; Gerbers generated for both PI and Stainless Steel Stiffener versions
2026-04-10 Solder mask expansion adjusted to 0mm for IC's and to -0.05mm for other components; Clearance with solder mask expansion set to 0.15mm for all components, PCB modified to comply with the clearance; G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
2026-04-13 BOM normalized (components unified under MPN)
2026-04-16 Pouring clearances increased to 0.2mm, pouring minumum width increased to 0.2mm; Gerbers generated
2026-04-18 CubeMX migration from nucleo to stm32f303cc; ADC sampling code also migrated (need to double check)
